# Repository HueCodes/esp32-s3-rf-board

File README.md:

# ESP32-S3 RF Dev Board

A 4-layer RF development board built around the bare ESP32-S3 QFN56 die (not a module),
featuring a designed-from-scratch 50-ohm microstrip RF path, CP2102 USB-UART bridge, and
AP2112K LDO power supply.

Board dimensions: **50 x 40 mm**. Stackup: **JLC04161H-7628** (JLCPCB standard 4-layer).

[Blog write-up](https://huecodes.github.io/hardware/esp32-s3-rf-board/)

---

## Why bare die, not a module?

ESP32 modules (WROOM, MINI) integrate a shielded RF section and a PCB trace antenna. They
handle the hard parts so you never have to think about transmission-line matching or antenna
keepouts. Using the bare QFN56 die means designing the RF path from scratch:

- Controlled-impedance microstrip trace from the chip RF pin to the antenna
- Solid GND plane on L2 to define a consistent reference for that trace
- Antenna keepout zones on every layer to prevent detuning from nearby copper
- GND stitching vias at lambda/10 intervals to suppress parallel-plate waveguide modes

The board is deliberately compact (50x40 mm) to make these constraints harder to satisfy.

---

## Block diagram

```
USB-C (J1)
  |
  |-- 5V --> AP2112K LDO --> 3.3V ---- ESP32-S3 (U1)
  |                                         |-- RF pin --> 50-ohm trace --> ANT1 (chip)
  |-- USB D+/D- --> CP2102 (U3) --> UART TX/RX           |-> J2 (u.FL test port)
                                         |
                                         |-- GPIO48 --> D1 (status LED)
                                         |-- UART  --> J3 (2.54mm header)
                                         |-- I2C   --> J4
                                         |-- SPI   --> J5
```

---

## RF design

### Trace impedance

The RF trace runs on L1 (F.Cu) over the solid GND plane on L2 (In1.Cu). The dielectric
separating them is 0.2 mm of JLC4161H 7628 prepreg (Er = 4.4).

Microstrip impedance formula (IPC-2141A approximation):

```
Z0 = (87 / sqrt(Er + 1.41)) * ln(5.98h / (0.8w + t))

h = 0.2 mm (dielectric thickness)
w = 0.6 mm (trace width)
t = 0.035 mm (copper thickness, 1 oz)
Er = 4.4

Z0 ≈ 50 ohm
```

Verified against Saturn PCB Toolkit. A ±10% width tolerance (0.06 mm) shifts impedance by
roughly ±3 ohm, acceptable for a 2.4 GHz short trace.

### Antenna keepout

The Johanson 2450AT18A100 datasheet specifies a copper-free zone around the antenna to
prevent nearby copper from loading the antenna and shifting its resonant frequency. The
implementation uses a **5 mm radius keepout polygon on F.Cu, B.Cu, and In1.Cu**, generated
programmatically in `generate_board.py`.

In1.Cu (GND plane) has an identical 5 mm cutout directly beneath the antenna. This is the
most critical layer: a solid GND plane under the antenna would short its near-field and
collapse radiation resistance.

### GND stitching vias

Stitching vias connect F.Cu ground pours to the In1.Cu GND plane at ~6 mm intervals along
both sides of the RF trace. At 2.4 GHz, lambda in FR4 ≈ 60 mm, so 6 mm is lambda/10 — the
threshold above which via spacing starts to allow resonant slots.

### u.FL test port (J2)

J2 allows connecting a VNA or spectrum analyser during bring-up to measure the actual
delivered power and check return loss (S11). The chip antenna and u.FL port share the
RF_ANT net. Fitting a 0-ohm series jumper (or DNP one side) selects which path is active.

---

## PCB stackup

| Layer | Function | Copper | Dielectric |
|-------|----------|--------|------------|
| L1 F.Cu | Signals, RF trace, components | 35 um | — |
| Prepreg 1 | JLC4161H 7628 | — | 0.2 mm, Er=4.4 |
| L2 In1.Cu | Solid GND plane | 35 um | — |
| Core | FR4 | — | 1.065 mm, Er=4.5 |
| L3 In2.Cu | 3.3V power plane | 35 um | — |
| Prepreg 2 | JLC4161H 7628 | — | 0.2 mm, Er=4.4 |
| L4 B.Cu | Secondary signals | 35 um | — |
| **Total** | | | **1.6 mm** |

Separating GND (L2) and power (L3) onto dedicated inner layers keeps L1/L4 free for signals
and provides low-impedance return paths directly under every trace.

---

## Power supply

The AP2112K-3.3V LDO converts 5V USB power to 3.3V for all ICs.

- Input bulk: 10 uF X5R 0805 (C7) — handles transient current demand during WiFi TX bursts
- Output bulk: 10 uF X5R 0805 (C8) — keeps output stable during load steps
- Local decoupling: 100 nF X5R 0402 caps within 2 mm of each VCC pin (C1-C6, C9-C11)

ESP32-S3 peak current: ~350 mA during WiFi TX. AP2112K rated 600 mA. Margin: ~250 mA.

### USB-C CC resistors

USB-C requires 5.1 kohm pull-downs on CC1 and CC2 for the device to be recognised by a
charger/host. R3 and R4 (5.1k 0402) are placed adjacent to J1 and pull CC1/CC2 to GND.

### USB ESD protection

U4 (USBLC6-2SC6, SOT-23-6) clamps D+ and D- against ESD events. Placed between J1 and U3
on the USB data path.

### Test points

TP1 (3.3V), TP2 (GND), and TP3 (RF_ANT) are 1.5mm SMD pads for probe access during
bring-up without needing to touch 0402 component pads.

---

## Firmware

See [`firmware/`](firmware/) for the ESP-IDF project.

The firmware demonstrates the board working end-to-end:

- WiFi station mode scan — validates the RF path is functional
- Scan results printed via UART at 115200 baud — visible on J3 or via CP2102 USB port
- Status LED (GPIO48) blinks at 1 Hz to indicate the CPU is running

### Prerequisites

- ESP-IDF v5.x (`idf.py` on PATH)
- USB cable connected to J1 (CP2102 provides UART over USB)

### Build and flash

```sh
cd firmware
idf.py set-target esp32s3
idf.py build
idf.py -p /dev/ttyUSB0 flash monitor
```

Expected UART output:

```
I (352) rf-board: ESP32-S3 RF Board - firmware v1.0.0
I (362) rf-board: Starting WiFi scan...
I (2512) rf-board: --- WiFi Scan: 8 networks found ---
I (2512) rf-board:   [ 1] RSSI  -42 dBm  CH  6  MyNetwork
I (2512) rf-board:   [ 2] RSSI  -67 dBm  CH 11  Neighbour_2G
...
```

---

## PCB generation scripts

The KiCAD project files are generated programmatically rather than drawn by hand. This makes
design parameters (trace widths, component positions, keepout radii) version-controlled and
reproducible.

| Script | Purpose |
|--------|---------|
| `generate_board.py` | Generates `.kicad_pcb`, `.kicad_pro`, `.kicad_sch`, `bom.csv` from scratch |
| `reroute_clean.py` | Re-runs routing with updated component positions |
| `fix_pcb.py` | Post-processes PCB file: adds missing UUIDs, fixes zone fill syntax |

```sh
# Regenerate the full project (outputs to current directory by default)
python generate_board.py

# Write to a specific directory
python generate_board.py --output /path/to/project

# Verbose logging
python generate_board.py --verbose
```

---

## Bill of materials

See [`bom.csv`](bom.csv) for full BOM with JLCPCB part numbers.

Key components:

| Ref | Part | Package | Notes |
|-----|------|---------|-------|
| U1 | ESP32-S3FN8 | QFN56 7x7 | Dual-core LX7, 2.4GHz WiFi/BT5, 8 MB internal flash |
| U2 | AP2112K-3.3V | SOT-23-5 | 600 mA LDO |
| U3 | CP2102-GMR | QFN28 5x5 | USB Full-Speed to UART |
| U4 | USBLC6-2SC6 | SOT-23-6 | USB ESD protection |
| Y1 | NX3225GA-40.000MHz | SMD 3.2x2.5 | ESP32-S3 main clock (10 ppm) |
| ANT1 | Johanson 2450AT18A100 | 0402 | 50-ohm chip antenna |
| J2 | u.FL SMD | -- | RF test port |
| R3, R4 | 5.1k 0402 | 0402 | USB CC1/CC2 pull-downs |
| R5 | 10k 0402 | 0402 | EN pull-up to 3V3 |
| R6, R7 | 22R 0402 | 0402 | USB D+/D- series damping |
| C12, C13 | 12pF NP0 0402 | 0402 | Crystal load caps |
| TP1-TP3 | Test points | 1.5mm pad | 3V3, GND, RF_ANT |

---

## Repository structure

```
esp32-s3-rf-board/
├── firmware/                   # ESP-IDF firmware project
│   ├── main/
│   │   ├── main.c              # App entry point
│   │   ├── hw_config.h         # Pin and peripheral definitions
│   │   └── CMakeLists.txt
│   ├── CMakeLists.txt
│   └── sdkconfig.defaults
├── esp32-s3-rf-board.kicad_pcb # PCB layout
├── esp32-s3-rf-board.kicad_pro # Project / design rules
├── esp32-s3-rf-board.kicad_sch # Schematic
├── bom.csv                     # Bill of materials
├── generate_board.py           # PCB generator
├── reroute_clean.py            # Routing script
├── fix_pcb.py                  # Post-processing
└── ESP32-S3-RF-Board-Learning-Guide.md
```

---

## Known limitations (v1.2)

- The schematic is generated programmatically rather than hand-drawn. Symbols
  and nets are real and ERC passes with 0 errors; the remaining 110 warnings
  are cosmetic (off-grid labels, library registration, footprint link
  strings). A GUI pass would clean these up and improve readability.
- Only the pins used by the current design are modelled on the ESP32-S3
  schematic symbol. The PCB footprint has all 57 pads; strapping pins other
  than IO0 are left at their power-on defaults (SPI flash boot, 3.3V).
- **PCB DRC: 33 placement warnings + 120 unconnected nets**. All shorts,
  clearance, and keepout errors have been resolved programmatically. The
  remaining warnings are courtyard overlaps (16), silk-over-copper (15),
  and dangling vias (2) -- none are electrical problems. The 120
  unconnected items are signal/power nets that need routing in Pcbnew
  before Gerber export. Recommended sequence:
  1. Open the PCB in KiCad 9.
  2. Route the remaining nets (mostly power, USB, UART/I2C/SPI fanout).
  3. `kicad-cli pcb drc ...` should report 0 unconnected items before fab.

### DRC progress (for reference)

| Stage | Violations | Unconnected |
|-------|-----------:|------------:|
| Pre-v1.2 baseline      | 447 | 70  |
| After crystal/flash/sch fixes (initial v1.2) | 144 | 122 |
| After programmatic DRC cleanup (final v1.2)  |  33 | 120 |

### Resolved in v1.2

- 40 MHz crystal (Y1, NX3225GA) with 2x 12 pF NP0 load caps (C12, C13) on
  the ESP32-S3 XTAL_P / XTAL_N pins. Without this the chip has no clock.
- U1 changed from generic ESP32-S3 (no flash) to **ESP32-S3FN8** with 8 MB
  of internal flash. No external SPI flash needed; boots directly.
- EN pull-up (R5, 10 kΩ) to 3V3 so the reset button has something to pull
  against and the chip is enabled at power-on.
- 22 Ω series resistors (R6, R7) on USB D+/D- near the CP2102 to damp
  reflections on the full-speed differential pair.
- Decoupling caps repositioned so every VDD pad has a 100 nF cap within
  2 mm of pin centre.
- Real schematic with symbols + nets generated by `generate_board.py`.

### Resolved in v1.1

- CC1/CC2 5.1k pull-down resistors (R3, R4) added for USB power negotiation.
- ESD protection (U4, USBLC6-2SC6) added on USB D+/D-.
- Test points (TP1-TP3) added for 3.3V, GND, and RF_ANT.

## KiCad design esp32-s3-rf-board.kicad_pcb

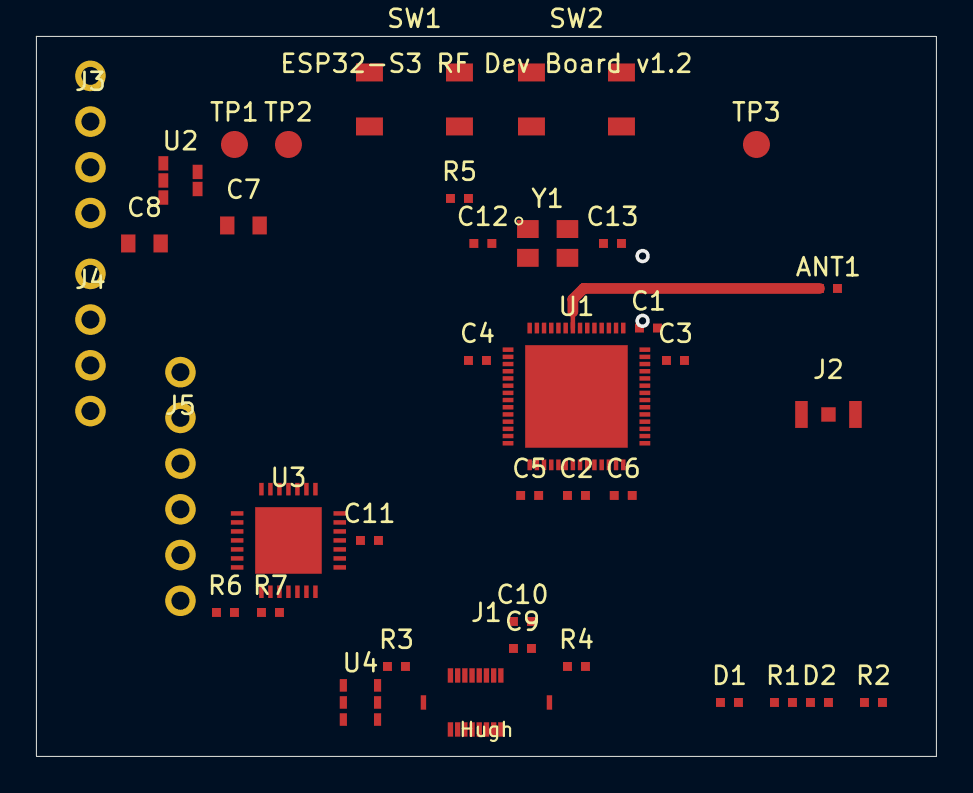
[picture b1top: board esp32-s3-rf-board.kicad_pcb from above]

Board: 4 copper layers, 50.0 x 40.0 mm, 38 parts (0 on the bottom side), 25 nets.

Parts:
ANT1: 2450AT18A100; ANT1_fp
C1: 100nF; C1_fp
C2: 100nF; C2_fp
C3: 100nF; C3_fp
C4: 100nF; C4_fp
C5: 100nF; C5_fp
C6: 100nF; C6_fp
C7: 10uF; C7_fp
C8: 10uF; C8_fp
C9: 100nF; C9_fp
C10: 100nF; C10_fp
C11: 100nF; C11_fp
C12: 12pF; C12_fp
C13: 12pF; C13_fp
D1: LED_RED; D1_fp
D2: LED_GRN; D2_fp
J1: USB-C 16P; J1_fp
J2: u.FL; J2_fp
J3: UART_4P; J3_fp
J4: I2C_4P; J4_fp
J5: SPI_6P; J5_fp
R1: 330R; R1_fp
R2: 1k; R2_fp
R3: 5.1k; R3_fp
R4: 5.1k; R4_fp
R5: 10k; R5_fp
R6: 22R; R6_fp
R7: 22R; R7_fp
SW1: RST_BTN; SW1_fp
SW2: BOOT_BTN; SW2_fp
TP1: TP_3V3; TP1_fp
TP2: TP_GND; TP2_fp
TP3: TP_RF; TP3_fp
U1: ESP32-S3-WROOM; U1_fp
U2: AP2112K-3.3V; U2_fp
U3: CP2102-GMR; U3_fp
U4: USBLC6-2SC6; U4_fp
Y1: 40MHz; Y1_fp

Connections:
3V3: C1.1, C2.1, C3.1, C4.1, C5.1, C6.1, C8.1, C11.1, J3.2, J4.2, J5.2, R2.1, R5.1, TP1.1, U1.7, U1.8, U1.29, U2.5, U3.4, U3.15
5V: C7.1, C9.1, C10.1, J1.2, J1.7, J1.10, J1.15, U2.3, U4.5
EN: R5.2, SW1.3, SW1.4, U1.51, U2.1
GND: ANT1.2, C1.2, C2.2, C3.2, C4.2, C5.2, C6.2, C7.2, C8.2, C9.2, C10.2, C11.2, C12.2, C13.2, D1.K, D2.K, J1.1, J1.8, J1.9, J1.16, J1.17, J1.18, J2.2, J2.3, J3.1, J4.1, J5.1, R3.2, R4.2, SW1.1, SW1.2, SW2.1, SW2.2, TP2.1, U1.1, U1.4, U1.5, U1.6, U1.15, U1.43, U1.53, U1.54, U1.55, U1.56, U1.57, U2.2, U3.1, U3.8, U3.16, U3.22, U3.29, U4.2, Y1.2, Y1.4
GPIO0: SW2.3, SW2.4, U1.52
GPIO48_LED: R1.1, U1.48
I2C_SCL: J4.4, U1.23, U1.25
I2C_SDA: J4.3, U1.22, U1.24
LED_POWER_A: D2.A, R2.2
LED_STATUS_A: D1.A, R1.2
RF_ANT: ANT1.1, J2.1, TP3.1, U1.36
SPI_CS: J5.6, U1.19
SPI_MISO: J5.4, U1.17
SPI_MOSI: J5.3, U1.16
SPI_SCK: J5.5, U1.18
UART_RX: J3.4, U1.21, U3.10
UART_TX: J3.3, U1.20, U3.9
USB_CC1: J1.5, R3.1
USB_CC2: J1.13, R4.1
USB_DM: J1.3, J1.11, R7.2, U4.1, U4.6
USB_DM_CP: R7.1, U3.2
USB_DP: J1.4, J1.12, R6.2, U4.3, U4.4
USB_DP_CP: R6.1, U3.3
XTAL_N: C13.1, U1.40, Y1.3
XTAL_P: C12.1, U1.39, Y1.1

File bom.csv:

Ref,Value,Footprint,JLCPCB_Part,Qty,Description
"U1","ESP32-S3FN8","QFN-56_7x7mm_P0.4mm","C2913204",1,"ESP32-S3 WiFi BT SoC QFN56, 8MB internal flash"
"U2","AP2112K-3.3TRG1","SOT-23-5","C51118",1,"600mA LDO 3.3V output"
"U3","CP2102-GMR","QFN-28_5x5mm_P0.5mm","C6568",1,"USB to UART bridge"
"U4","USBLC6-2SC6","SOT-23-6","C7519",1,"USB ESD protection TVS diode array"
"Y1","40MHz_NX3225GA","XTAL_SMD_3225_4P","C9040",1,"40 MHz SMD crystal 3.2x2.5mm 4-pad, 10ppm"
"ANT1","2450AT18A100","ANT_0402_1x0.5mm","C167687",1,"2.4GHz chip antenna 50-ohm"
"J1","USB_C_16P","USB-C_SMD_16P","C165948",1,"USB-C receptacle 16-pin"
"J2","U.FL_SMD","U.FL_SMD","C88374",1,"u.FL/IPEX RF connector"
"J3","1x04 2.54mm","PinHeader_1x04_P2.54mm","C49661",1,"4-pin UART header"
"J4","1x04 2.54mm","PinHeader_1x04_P2.54mm","C49661",1,"4-pin I2C header"
"J5","1x06 2.54mm","PinHeader_1x06_P2.54mm","C124378",1,"6-pin SPI header"
"SW1","SW_TACT_6x6","SW_Tactile_6x6mm","C318884",1,"Reset tactile switch 6x6mm"
"SW2","SW_TACT_6x6","SW_Tactile_6x6mm","C318884",1,"Boot tactile switch 6x6mm"
"D1","LED_RED","LED_0402","C2286",1,"Red LED 0402 status"
"D2","LED_GRN","LED_0402","C2297",1,"Green LED 0402 power"
"R1","330R","R_0402","C23197",1,"330 ohm resistor 0402 (status LED)"
"R2","1k","R_0402","C11702",1,"1k ohm resistor 0402 (power LED)"
"R3","5.1k","R_0402","C25905",1,"5.1k ohm 1% 0402 USB CC1 pull-down"
"R4","5.1k","R_0402","C25905",1,"5.1k ohm 1% 0402 USB CC2 pull-down"
"R5","10k","R_0402","C25804",1,"10k ohm 0402 EN pull-up to 3V3"
"R6","22R","R_0402","C22975",1,"22 ohm 0402 USB D+ series resistor"
"R7","22R","R_0402","C22975",1,"22 ohm 0402 USB D- series resistor"
"TP1","TP_3V3","TP_SMD_1.5mm","C17228",1,"Test point 3.3V rail"
"TP2","TP_GND","TP_SMD_1.5mm","C17228",1,"Test point GND"
"TP3","TP_RF","TP_SMD_1.5mm","C17228",1,"Test point RF_ANT"
"C1,C2,C3,C4,C5,C6,C9,C10,C11","100nF","C_0402","C1525",9,"100nF 0402 decoupling capacitor"
"C7,C8","10uF","C_0805","C17024",2,"10uF 0805 bulk capacitor"
"C12,C13","12pF","C_0402","C1652",2,"12 pF NP0 0402 crystal load cap"

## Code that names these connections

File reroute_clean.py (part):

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    12: "SPI_MISO",
    13: "SPI_SCK",
    14: "SPI_CS",
    15: "GPIO48_LED",
    16: "EN",
    17: "GPIO0",
    18: "LED_STATUS_A",
    19: "LED_POWER_A",
    20: "USB_CC1",
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        29: "3V3",
        36: "RF_ANT",
        43: "GND",
        48: "GPIO48_LED",
        51: "EN", 52: "GPIO0",
        53: "GND", 54: "GND", 55: "GND", 56: "GND",
        57: "GND",
    }
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    lines.append(fp_text("value", label, 0, 4.5, "F.Fab"))
    lines.append(fp_courtyard_rect(-3.5, -3.5, 3.5, 3.5))
    lines.append(fp_fab_rect(-3.0, -3.0, 3.0, 3.0))
    net1 = "EN" if "RST" in label else "GPIO0"
    lines.append(smd_pad(1, -2.5, -1.5, 1.5, 1.0, "GND"))
    lines.append(smd_pad(2,  2.5, -1.5, 1.5, 1.0, "GND"))
    lines.append(smd_pad(3, -2.5,  1.5, 1.5, 1.0, net1))
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    add(route_45(ldo_vout_x, ldo_vout_y, r2_in_x, r2_in_y, PWR_W, "F.Cu", "3V3"))

    # -----------------------------------------------------------------------
    # UART_TX (net 7): ESP32 pad20 -> via -> B.Cu -> via -> CP2102 pad9 AND J3 pin3
    # ESP32 pad20 right side: i=20-15=5, py=20+(6.5-5)*0.4=20.6, px=33.8
    # CP2102 pad9: right side i=9-8=1, py=33+(3-1)*0.5=34.0, px=20+2.5+0.35=22.85
    # J3 pin3 (UART_TX): (3, 10+1.27) = (3, 11.27)
    # -----------------------------------------------------------------------
    esp_tx = esp_right(20)    # (33.8, 20.6)
    cp_tx_x = cpx + 2.5 + 0.35   # 22.85
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    add(route_via_bcu(esp_tx[0], esp_tx[1], j3_tx[0], j3_tx[1], "UART_TX", SIG_W))

    # -----------------------------------------------------------------------
    # UART_RX (net 8): ESP32 pad21 -> via -> B.Cu -> via -> CP2102 pad10 AND J3 pin4
    # ESP32 pad21: i=21-15=6, py=20+(6.5-6)*0.4=20.2, px=33.8
    # CP2102 pad10: right side i=10-8=2, py=33+(3-2)*0.5=33.5, px=22.85
    # J3 pin4 (UART_RX): (3, 10+3.81) = (3, 13.81)
    # -----------------------------------------------------------------------
    esp_rx = esp_right(21)
    cp_rx_x = cpx + 2.5 + 0.35
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    add(route_via_bcu(esp_rx[0], esp_rx[1], j3_rx[0], j3_rx[1], "UART_RX", SIG_W))

    # -----------------------------------------------------------------------
    # I2C_SDA (net 9): ESP32 pad22 -> B.Cu -> J4 pin3
    # ESP32 pad22: i=22-15=7, py=20+(6.5-7)*0.4=19.8, px=33.8
    # J4 pin3 (I2C_SDA): (3, 19+1.27) = (3, 20.27)
    # -----------------------------------------------------------------------
    esp_sda = esp_right(22)
    j4_sda  = (j4x, j4y + 1.27)
    add(route_via_bcu(esp_sda[0], esp_sda[1], j4_sda[0], j4_sda[1], "I2C_SDA", SIG_W))

    # -----------------------------------------------------------------------
    # I2C_SCL (net 10): ESP32 pad23 -> B.Cu -> J4 pin4
    # ESP32 pad23: i=23-15=8, py=20+(6.5-8)*0.4=19.4, px=33.8
    # J4 pin4 (I2C_SCL): (3, 19+3.81) = (3, 22.81)
    # -----------------------------------------------------------------------
    esp_scl = esp_right(23)
    j4_scl  = (j4x, j4y + 3.81)
    add(route_via_bcu(esp_scl[0], esp_scl[1], j4_scl[0], j4_scl[1], "I2C_SCL", SIG_W))

    # -----------------------------------------------------------------------
    # SPI_MOSI (net 11): ESP32 pad16 -> B.Cu -> J5 pin3
    # ESP32 pad16: i=16-15=1, py=20+(6.5-1)*0.4=22.2, px=33.8
    # J5 pin3 (SPI_MOSI): (3, 28-2.54) = (3, 26.73) ... actually (3, 28+(-2)*1.27) = (3,25.46)?
    # J5 6-pin: py = -(5/2)*2.54 + i*2.54; i=0..5
    # pin3 = i=2: py = -6.35 + 5.08 = -1.27 -> world y = 28-1.27 = 26.73
    # -----------------------------------------------------------------------
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    add(route_via_bcu(esp_mosi[0], esp_mosi[1], j5_mosi[0], j5_mosi[1], "SPI_MOSI", SIG_W))

    # -----------------------------------------------------------------------
    # SPI_MISO (net 12): ESP32 pad17 -> B.Cu -> J5 pin4
    # ESP32 pad17: i=2, py=20+(6.5-2)*0.4=21.8, px=33.8
    # J5 pin4 = i=3: py = -6.35+7.62 = 1.27 -> world y = 29.27
    # -----------------------------------------------------------------------
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    add(route_via_bcu(esp_miso[0], esp_miso[1], j5_miso[0], j5_miso[1], "SPI_MISO", SIG_W))

    # -----------------------------------------------------------------------
    # SPI_SCK (net 13): ESP32 pad18 -> B.Cu -> J5 pin5
    # ESP32 pad18: i=3, py=20+(6.5-3)*0.4=21.4, px=33.8
    # J5 pin5 = i=4: py = -6.35+10.16 = 3.81 -> world y = 31.81
    # -----------------------------------------------------------------------
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    add(route_via_bcu(esp_sck[0], esp_sck[1], j5_sck[0], j5_sck[1], "SPI_SCK", SIG_W))

    # -----------------------------------------------------------------------
    # SPI_CS (net 14): ESP32 pad19 -> B.Cu -> J5 pin6
    # ESP32 pad19: i=4, py=20+(6.5-4)*0.4=21.0, px=33.8
    # J5 pin6 = i=5: py = -6.35+12.7 = 6.35 -> world y = 34.35
    # -----------------------------------------------------------------------
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    add(route_via_bcu(esp_cs[0], esp_cs[1], j5_cs[0], j5_cs[1], "SPI_CS", SIG_W))

    # -----------------------------------------------------------------------
    # GPIO48_LED (net 15): ESP32 pad48 -> F.Cu -> R1 pad1 (input)
    # pad48: left side i=48-43=5, py=20-(6.5-5)*0.4=19.4, px=26.2
    # R1 at (POS_LED_STA[0]+1.5, POS_LED_STA[1]) = (21.5, 37.5), pad1 at rel(-0.5, 0) = (21, 37.5)
    # -----------------------------------------------------------------------
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    # Actually: esp_left(48): i=48-43=5, return (26.2, 20 - (6.5-5)*0.4) = (26.2, 19.4)
    r1_in_x = POS_LED_STA[0] + 1.5 - 0.5  # 21.0
    r1_in_y = POS_LED_STA[1]               # 37.5
    add(route_45(esp_led[0], esp_led[1], r1_in_x, r1_in_y, SIG_W, "F.Cu", "GPIO48_LED"))

    # -----------------------------------------------------------------------
    # LED_STATUS_A (net 18): R1 pad2 -> D1 pad A
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    add(route_45(esp_en[0], esp_en[1], sw1_x, sw1_y, SIG_W, "F.Cu", "EN"))

    # -----------------------------------------------------------------------
    # GPIO0 (net 17): ESP32 pad52 -> SW2 (BOOT button at 30, 3.5)
    # pad52: left side i=52-43=9, py=20-(6.5-9)*0.4=21.0, px=26.2
    # SW2 pad3 at rel(-2.5, 1.5) -> world (27.5, 5.0)
    # -----------------------------------------------------------------------
    esp_gpio0 = esp_left(52)   # (26.2, 21.0)
    sw2_x     = POS_BOOT_BTN[0] - 2.5   # 27.5
    sw2_y     = POS_BOOT_BTN[1] + 1.5   # 5.0
    add(route_45(esp_gpio0[0], esp_gpio0[1], sw2_x, sw2_y, SIG_W, "F.Cu", "GPIO0"))

    # -----------------------------------------------------------------------
    # GND: short stubs to connect J3/J4/J5 pin1 GND pads
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    parts.append(gen_led_0402("D1", POS_LED_STA[0] - 1.5, POS_LED_STA[1], "LED_STATUS_A", "LED_RED"))
    parts.append(gen_led_0402("D2", POS_LED_PWR[0] - 1.5, POS_LED_PWR[1], "LED_POWER_A",  "LED_GRN"))
    parts.append(gen_resistor_0402("R1", POS_LED_STA[0] + 1.5, POS_LED_STA[1],
                                   "GPIO48_LED", "LED_STATUS_A", "330R", "330R"))
    parts.append(gen_resistor_0402("R2", POS_LED_PWR[0] + 1.5, POS_LED_PWR[1],
                                   "3V3", "LED_POWER_A", "1k", "1k"))

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
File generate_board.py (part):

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POS_SPI     = (8.0,  25.0)   # 6-pin SPI header offset to x=8 so its pins
                             # don't collide with J4 at x=3
POS_RST_BTN = (21.0, 3.5)    # Reset button
POS_BOOT_BTN= (30.0, 3.5)    # Boot button (GPIO0)
POS_LED_STA = (40.0, 37.0)   # Status LED (moved away from new USB-C)
POS_LED_PWR = (45.0, 37.0)   # Power LED
POS_ESD     = (18.0, 37.0)   # USBLC6-2SC6 ESD protection (between CP2102 and new USB-C)
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    12: "SPI_MISO",
    13: "SPI_SCK",
    14: "SPI_CS",
    15: "GPIO48_LED",
    16: "EN",
    17: "GPIO0",
    18: "LED_STATUS_A",
    19: "LED_POWER_A",
    20: "USB_CC1",
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        40: "XTAL_N",
        # Left side (pads 43-56, top to bottom)
        43: "GND",
        48: "GPIO48_LED",
        51: "EN", 52: "GPIO0",
        53: "GND", 54: "GND", 55: "GND", 56: "GND",
        # Exposed pad
        57: "GND",
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    lines.append(fp_fab_rect(-3.0, -3.0, 3.0, 3.0))
    # 4 pads: 2 on each side
    net = "GND" if "RST" in label or "BOOT" in label else ""
    net1 = "EN" if "RST" in label else "GPIO0"
    lines.append(smd_pad(1, -2.5, -1.5, 1.5, 1.0, "GND"))
    lines.append(smd_pad(2,  2.5, -1.5, 1.5, 1.0, "GND"))
    lines.append(smd_pad(3, -2.5,  1.5, 1.5, 1.0, net1))
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def gen_esd_usblc6(ref, x, y):
    """
    USBLC6-2SC6 ESD protection in SOT-23-6 package.
    Pinout: 1=I/O1 (USB_DM), 2=GND, 3=I/O2 (USB_DP),
            4=I/O2 (USB_DP), 5=VBUS (5V), 6=I/O1 (USB_DM)
    Clamps USB D+/D- to safe levels against ESD events.
    """
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    lx, ly = POS_LDO
    lines.append(gen_cap_0805("C7", lx + 3.5, ly + 2.5, "5V", "GND", "10uF"))
    # 10uF bulk cap at LDO output (3V3 side); offset down-right so its pads
    # don't collide with U2 pad 3 (5V) or J3 pin 4 (UART_RX).
    lines.append(gen_cap_0805("C8", lx - 2.0, ly + 3.5, "3V3", "GND", "10uF"))

    # 100nF bypass caps for USB-C power lines
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    parts.append(gen_led_0402("D1", POS_LED_STA[0] - 1.5, POS_LED_STA[1], "LED_STATUS_A", "LED_RED"))
    parts.append(gen_led_0402("D2", POS_LED_PWR[0] - 1.5, POS_LED_PWR[1], "LED_POWER_A",  "LED_GRN"))
    parts.append(gen_resistor_0402("R1", POS_LED_STA[0] + 1.5, POS_LED_STA[1],
                                   "GPIO48_LED", "LED_STATUS_A", "330R", "330R"))
    parts.append(gen_resistor_0402("R2", POS_LED_PWR[0] + 1.5, POS_LED_PWR[1],
                                   "3V3", "LED_POWER_A", "1k", "1k"))

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    ("39", "XTAL_P"),
    ("40", "XTAL_N"),
    ("51", "CHIP_PU"),      # EN
    ("52", "IO0"),          # GPIO0 (boot strap)
    ("1",  "GND"),
    ("4",  "GND"),
    ("15", "GND"),
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    "SPI_MOSI", "SPI_MISO", "SPI_SCK", "SPI_CS",
    "UART_TX", "UART_RX",
    "I2C_SDA", "I2C_SCL",
    "GPIO48_LED",
]
ESP32_RIGHT_NETS = [
    "RF_ANT", "XTAL_P", "XTAL_N",
    "EN", "GPIO0",
    "GND", "GND", "GND", "GND", "GND", "GND",
]

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    ))
    placements.append(sch_instance_ic(
        "SW_Tactile", "SW2", "SW_TACT_6x6", "SW_Tactile_6x6mm",
        270, 170, ["GND", "GPIO0"], ["GND", "GPIO0"], 2, 2,
    ))

    # LEDs + series resistors (bottom-left of ESP32)
    placements.append(sch_instance_passive("LED", "D1", "LED_RED", "LED_0402",
                                           130, 200, "LED_STATUS_A", "GND"))
    placements.append(sch_instance_passive("R", "R1", "330R", "R_0402",
                                           130, 180, "GPIO48_LED", "LED_STATUS_A"))
    placements.append(sch_instance_passive("LED", "D2", "LED_GRN", "LED_0402",
                                           160, 200, "LED_POWER_A", "GND"))
    placements.append(sch_instance_passive("R", "R2", "1k", "R_0402",
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
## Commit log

2026-03-24 feat: 4-layer ESP32-S3 RF PCB design and BOM
    50-ohm microstrip feedline, Johanson 2450AT18A100 chip antenna
    with keepout zones, CP2102 USB-UART, AP2112K LDO. BOM includes
    JLCPCB part numbers for assembly.
2026-03-24 feat: reproducible board generation and routing scripts
    Python scripts for programmatic PCB generation, trace routing,
    rerouting, and design rule fixes. Enables reproducible builds
    without manual KiCad editing.
2026-03-24 feat: ESP-IDF WiFi scan validation firmware
    WiFi scan firmware for verifying RF path and antenna performance.
    Includes sdkconfig defaults for ESP32-S3 target.
2026-03-24 docs: README, blog writeup, and RF design learning guide
    Covers impedance calculations, microstrip geometry, antenna
    keepout rules, and GND stitching via spacing rationale.
2026-04-19 v1.2: 40 MHz crystal, ESP32-S3FN8 flash, real schematic
    Closes the three fab-blockers for the bare QFN56 design. Adds Y1
    (40 MHz NX3225GA) with C12/C13 12 pF NP0 load caps on XTAL_P/XTAL_N,
    swaps U1 to ESP32-S3FN8 (8 MB internal flash, same QFN56 footprint),
    and replaces the placeholder .kicad_sch with real symbols + nets
    (ERC: 0 errors). Also adds EN 10k pull-up (R5), USB 22R series damping
    (R6, R7), decaps repositioned within 2 mm of every VDD pad, and the
2026-04-20 v1.2: programmatic DRC cleanup -- 144 -> 33 violations, 0 shorts
    Fix the structural issues left over from the auto-generator:
    - RF trace: narrow fanout from pad 36 (0.25 mm) widening to 0.6 mm once
    clear of adjacent top-row pads, then vertical stub -> 45-deg -> horizontal.
    - RF keepout on F.Cu relaxed to copperpour-only (antenna pads and feed
    trace now allowed; In1.Cu and B.Cu still fully blocked).
    - Stitching vias: bumped perpendicular offset 1.2 -> 1.8 mm, dropped the
